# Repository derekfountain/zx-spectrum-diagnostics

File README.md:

# 16K/48K ZX Spectrum Diagnostics Board

This is a hardware diagnostics board for the 16K and 48K ZX Spectrum,
based on two Raspberry Pi Pico microcontroller boards.

The idea is that given a Spectrum of unknown provenance (an eBay
purchase maybe), this device can quickly tell you what potential
issues the Spectrum might have. It's limited to what it can see on the
rear edge connector, so it can't detect broken tracks or things like
that, but it can report a fair amount of useful information. There are
no guarantees, of course.

The board plugs into the Spectrum's rear edge connector, and has an OLED
screen and a single user-interface button:

The rear of the board carries the Picos and some header sockets (discussed below):

The board is powered by the Spectrum. You just plug it in and turn the
Spectrum on. It will (repeatedly) run a set of tests on the signals it
sees on the rear edge connector. The tests are divided into pages. Pressing
the button advances to the next page of tests.

Click through for a brief demonstration:

https://www.youtube.com/watch?v=3YdgdeM5kM0

## Status

As of March 2024, v1.2 is functionally complete. The KiCAD project here is current up
to v1.3 which just has a couple of silkscreen fixes.

There is plenty of scope to upgrade the tests the board runs, so updates
might appear in future. For now the board is complete.

[Derek Fountain](https://www.derekfountain.org/), March 2024

# Operation

The Spectrum is usable when the device is displaying the voltages page.
The tests which run on the other pages constantly reset the Spectrum
so it can't be used when any of those are showing.

The pages, and the tests run, are as follows. You might find it useful to
read the [Spectrum Service manual](https://spectrumforeveryone.com/wp-content/uploads/2017/08/ZX-Spectrum-Service-Manual.pdf)
in conjunction with the following.

## Voltages Page

Voltages are the first thing we look at when faced with a broken ZX Spectrum.
There are four voltages used: the input from the PSU, which is nominally +9V
and isn't analysed by the Picos; the main +5V supply for the Spectrum board;
the +12V supply for the RAM and video subsystem; and the -5V supply for the
RAM.

The OLED screen shows the voltages on the rear edge connector.
That's not the same as what's going on at the RAM chips! But it's a very good
indication, especially when you see faults being reported.

The top three lines of the display show the voltages as detected by the Pico's
analogue to digital converters. These values update several times a second. The
bottom three lines show the averages for those values over the last 100
samples. Note that the further the voltages get from the expected values, the
less accurate the reported values will be. This is because the circuitry on the
board is designed to protect the Picos from rogue voltages, as opposed to
providing accurate results in all circumstances.

The Picos are powered from the Spectrum's +5V so if that's not working
the Picos won't turn on and you probably won't have got this
far. Assuming the plug on the PSU is outputting 9V to 14V as you'd
expect, you probably have a faulty 7805 regulator.

The +12V and -5V supplies come from the Spectrum's internal DC/DC
converters. They're known to be a bit wobbly, and the -5V supply in particular
has a rather wide tolerance (-5.5V to -4.0V, see the service manual).

Here's a screen showing the voltages from a broken Spectrum. The -5V supply is
within specification, but the 12V supply is broken:

Note: if the Spectrum's internal voltage regulator has failed in such
a way that the Spectrum's internal +5V supply is too high, that high
voltage will be fed into the Picos and might destroy them. The maximum
they can take is +5.5V. I've never heard of a 7805 regulator failing
in this way, and if one does the Spectrum it's inside will be very
dead, but if you think it might have happened you should check the +5V
on the edge connector before connecting the Picos to it. (Remove the
Picos, plug the board in to the Spectrum, then check the +5V line at
any of the +5V sample points.)

## ULA Page

The ULA does a lot of stuff inside the Spectrum, and can fail in whole
or in part. i.e. some parts of its internal circuitry can be working while other
parts are dead. A partially working ULA can be rather puzzling to
diagnose. The tests on the diagnostics board only test the clocks the
ULA is emitting.

The INT clock is the Spectrum's interrupt clock. It's used to generate
both the TV picture and the Z80's interrupt signal. What's sampled
from the edge connector is directly from the ULA and should be exactly
50Hz.

The CLK is the Z80's clock, which is also generated by the ULA. This should be
3.5MHz. The diagnostics board samples the signal using the RP2040's PIOs, and
is (internally) accurate to a single clock cycle. This is sampled with the Z80
held in reset, so the Spectrum's notorious memory contention doesn't get in
the way (see next item).

The cCLK is the contended clock, which is the clock signal the ULA provides for
the Z80 when the ULA and memory chips clash trying to read lower memory. This will
always be slightly slower than the CLK signal. This is sampled when the Z80 is
allowed to run normally, which means the ROM code is running and is updating
the screen and system variables which are in lower RAM. Some contention should
always be reported. Holding the space key down while the test is running
changes the contention pattern:

## Z80 Page

A subset of the Z80 signals are exposed on the Spectrum's rear edge connector:
read, write, memory read, and I/O request. Their exact behaviour aren't analysed (but
could be).

The Spectrum is allowed to start normally, then the Z80 signals are checked to ensure
they are transiting from low to high state, and from high to low state. Any
stuck signal will be reported, and would explain a failure of the Spectrum. Look for
solder bridges from botched repairs, or broken tracks.

The M1 line is an exception. Sinclair used some Z80s with non-functioning M1 signals,
and machines with those faulty Z80s can't drive certain peripherals like the Interface
One and my [recreated ZX Spectrum Expansion System](https://www.derekfountain.org/zses.php). The Spectrum can otherwise function
correctly, so a fault reported with the M1 line isn't that unusual and doesn't indicate
a fault which would stop the machine working.

## Data Bus Page

This test allows the Spectrum to start normally, then the Z80 data bus signals are
checked to ensure they are transiting from low to high state, and from high to low
state. Any stuck signal will be reported, and would explain a failure of the Spectrum.
The most likely cause would be a faulty memory chip holding its output bit high or
low, but also look for solder bridges from botched repairs, or broken tracks.

If the Spectrum has a faulty ROM or some other unusual fault it would still be likely
that whatever was appearing on the data bus would consist of state changes of all the
lines, at least occasionally. Therefore this test should be able to indicate stuck
lines reasonably reliably even in the presence of other faults.

## Address Bus Page

This test allows the Spectrum to start normally, then the Z80 address bus signals are
checked to ensure they are transiting from low to high state, and from high to low
state. Any stuck signal will be reported, and would explain a failure of the Spectrum.

The early code in the Spectrum's ROM does a RAM check which writes and reads from the
whole 64K address space, so all the address lines should transit within a second or so
of the machine starting up.

The ULA's signals on the address bus aren't exposed on the edge connector. What is
reported here is the Z80's perspective.

## ROM Page

This page runs a single test which checks whether the ROM appears to be providing
the correct data to the Z80 (i.e. the program which implements the Spectrum's BASIC
interpreter).

It allows the Spectrum to start, then samples the address bus watching for reads of
bytes from the ROM. Those addresses are collected, then analysed to see if they follow
the expected pattern. The Z80 code at the start of the Spectrum's ROM disables
interrupts, primes a couple of registers, then jumps to an absolute (hardcoded)
location. It's therefore possible to check whether the Z80 is requesting the bytes at
0x0000 to 0x0007 one at a time in sequence, then requests the byte at 0x11CB (which is
where the jump goes to) and so on.

It only samples a couple of dozen addresses to check the Z80 is following the expected
sequence, but if it is that means the Z80, and its control, data and address buses
are all functioning correctly or very close to correctly.

# ZX Signal Headers

The board has 3 rows of 20 pins which make accessible the Z80 and
Spectrum control signals which are on the rear edge connector, plus a
few more from the board itself.  They're labelled J201, J202 and
J203. All except one (~12V) of the Spectrum's edge connector signals
are brought out to these connectors (and that missing ~12V line could
now be fixed because after a juggle around I found a couple of spare
connections - see the errata.txt file).

These headers allow jumper wires to be inserted which enable easy
connection to a meter or oscilloscope. I've found this very
handy. This photo shows oscilloscope probing of the Z80 clock and
another signal from a board I got from eBay. Note the silver tab on
the corner of the board is a ground point for attaching clips to.

# Bill of Materials

This is a simple build. You will need:

3x [3216 SMD Diode](https://www.mouser.co.uk/ProductDetail/581-SD1206S040S2R0)
Schottky Diode for Pico input protection and 12V clamping
<br>
1x [PMBT2222A SMD Transistor](https://www.mouser.co.uk/ProductDetail/771-PMBT2222A-T-R)
NPN Transistor for /RESET
<br>
1x [3216 SMD 1K Resistor](https://www.mouser.co.uk/ProductDetail/603-RT1206FRE071KL)
1K Resistor for /RESET
<br>
3x [3216 SMD 1K5 Resistor](https://www.mouser.co.uk/ProductDetail/603-RT1206FRE071K5L)
1K5 Resistor for the voltage dividers
<br>
1x [3216 SMD 390R Resistor](https://www.mouser.co.uk/ProductDetail/603-RT1206FRE07390RL)
390R Resistor for the voltage divider
<br>
1x [3216 SMD 5K6 Resistor](https://www.mouser.co.uk/ProductDetail/603-RT1206FRE075K6L)
5K6 Resistor for the voltage divider
<br>

Also, from your parts bin:

2x Raspberry Pi Pico with pins and sockets if you want them
<br>
1x 4-pin header and socket for mounting the screen
<br>
1x SPST switch. Any single pole, single throw switch should do for the user input
<br>
1x 0.96" OLED display (SSH1106 based if you want to use my code)

Note that the OLED screen I used is SSH1106 based. It's actually got SSD1306
printed on it, which was an unpleasant surprise at the time. If you want to
use one of the more common SSD1306 based screens the software will need
updating. It's only displaying text so that shouldn't be too difficult.

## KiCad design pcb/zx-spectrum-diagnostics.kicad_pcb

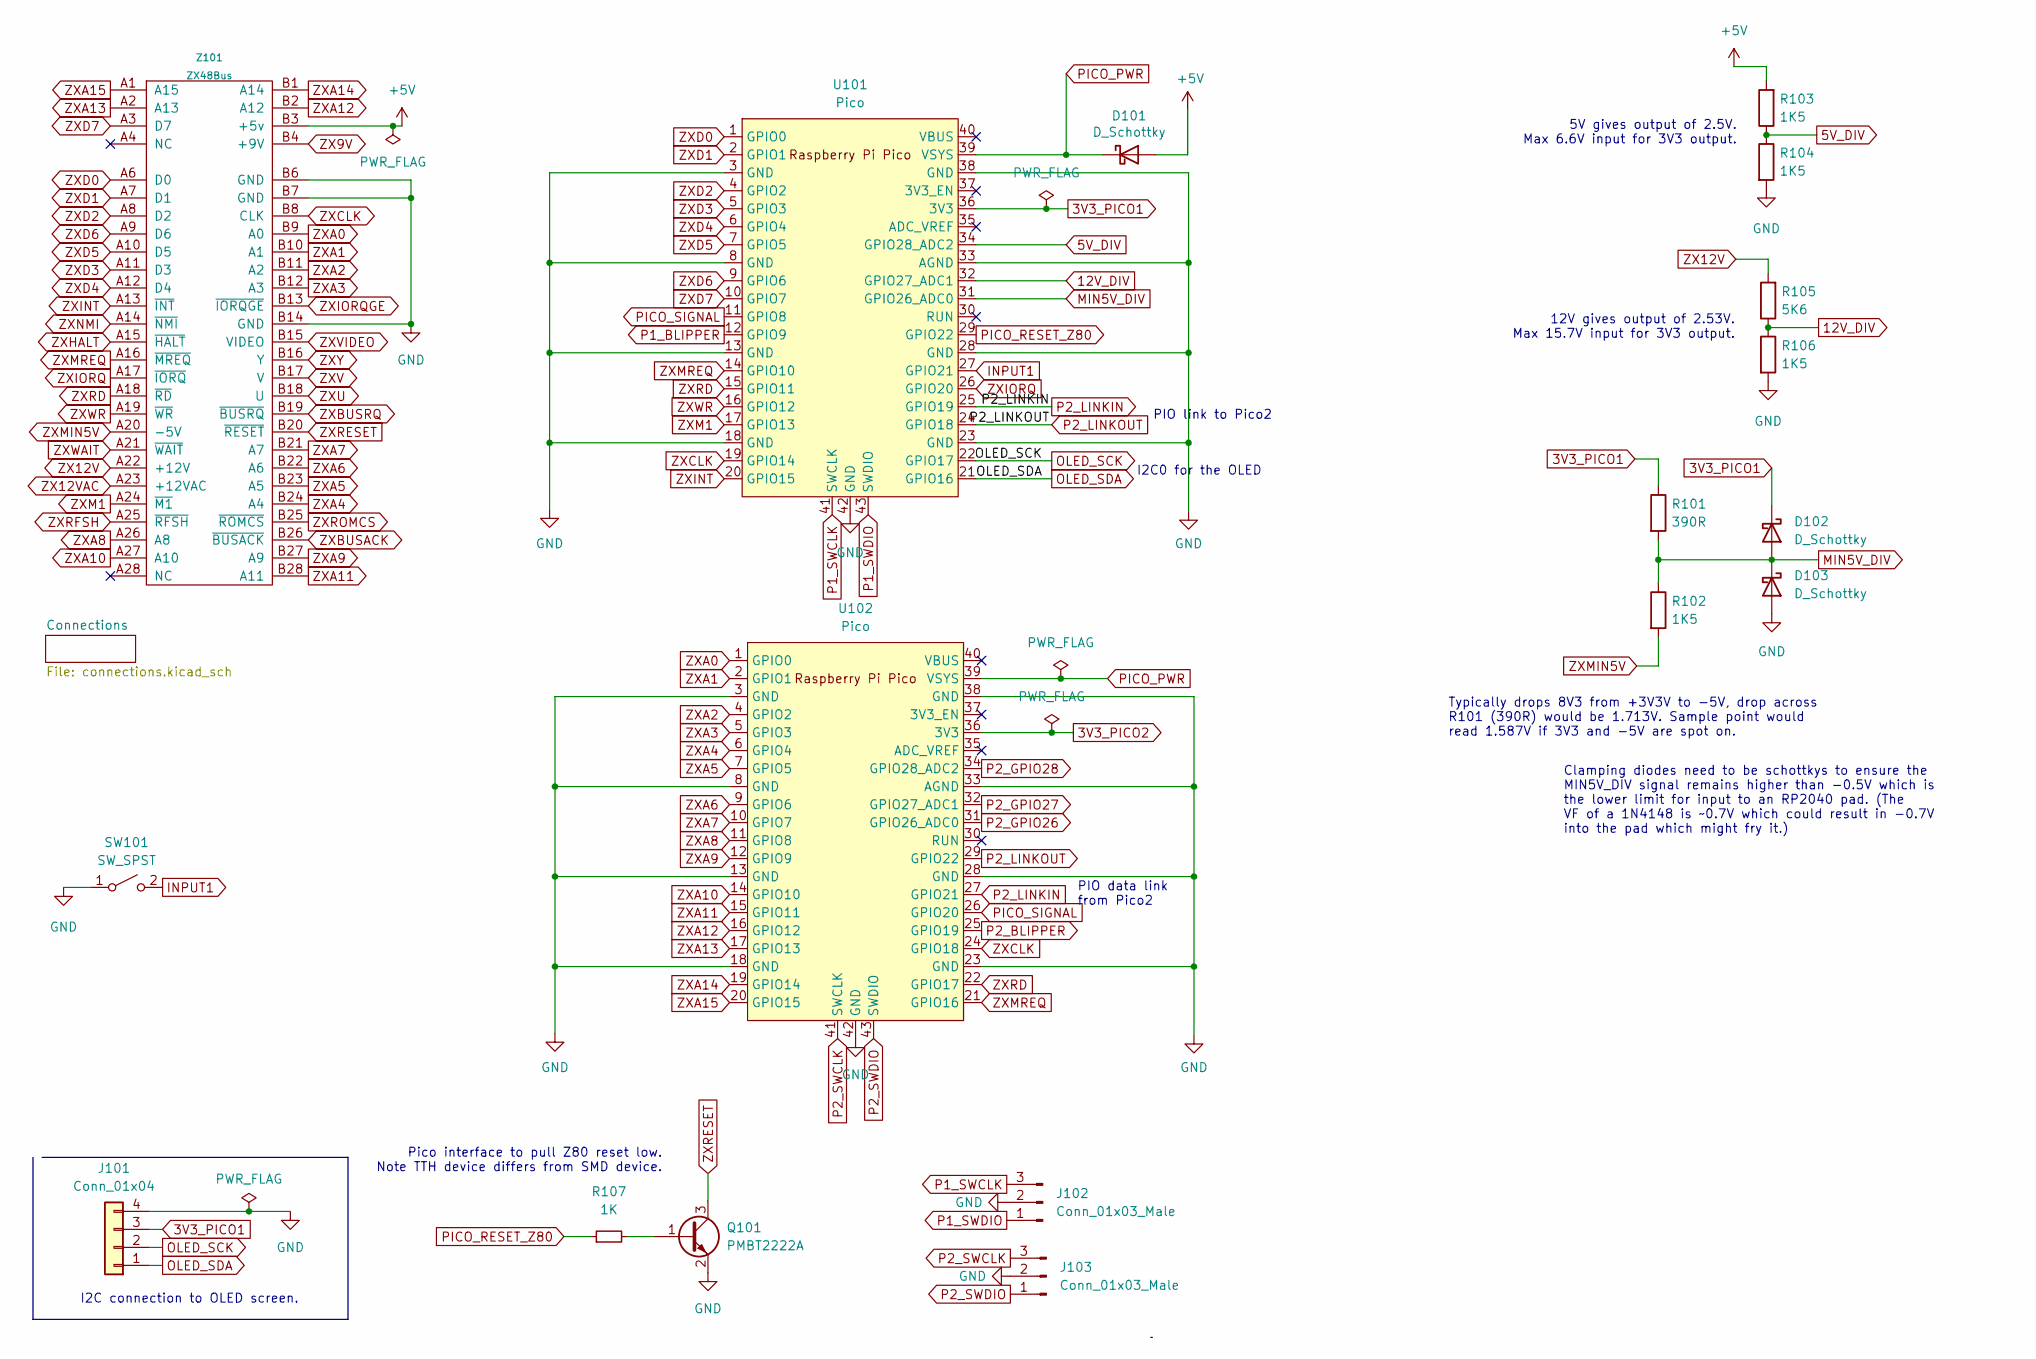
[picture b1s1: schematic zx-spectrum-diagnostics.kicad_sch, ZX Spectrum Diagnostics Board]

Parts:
D101, D102, D103: D_Schottky; D_1206_3216Metric_Pad1.42x1.75mm_HandSolder
J101: Conn_01x04; PinHeader_1x04_P2.54mm_Vertical
J102, J103: Conn_01x03_Male; PinSocket_1x03_P2.54mm_Vertical
Q101: PMBT2222A; TSOT-23_HandSoldering
R101: 390R; R_1206_3216Metric_Pad1.30x1.75mm_HandSolder
R102, R103, R104, R106: 1K5; R_1206_3216Metric_Pad1.30x1.75mm_HandSolder
R105: 5K6; R_1206_3216Metric_Pad1.30x1.75mm_HandSolder
R107: 1K; R_1206_3216Metric_Pad1.30x1.75mm_HandSolder
SW101: SW_SPST; SW_PUSH_6mm_H4.3mm
U101, U102: Pico; RPi_Pico_SMD_TH
Z101: ZX48Bus; Spectrum_Edge_Connector

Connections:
3V3_PICO1: D102.1 (K), J101.3, R101.1, U101.36 (3V3)
3V3_PICO2: U102.36 (3V3)
5V_DIV: R103.1, R104.1, U101.34 (GPIO28_ADC2); also elsewhere on the board
12V_DIV: R105.1, R106.1, U101.32 (GPIO27_ADC1); also elsewhere on the board
+5V: D101.2 (A), R103.2, Z101.B3 (+5v); also elsewhere on the board
GND: D103.2 (A), J101.4, J102.2, J103.2, Q101.2 (E), R104.2, R106.2, SW101.1 (A), U101.3 (GND), U101.8 (GND), U101.13 (GND), U101.18 (GND), U101.23 (GND), U101.28 (GND), U101.33 (AGND), U101.38 (GND), U101.42 (GND), U102.3 (GND), U102.8 (GND), U102.13 (GND), U102.18 (GND), U102.23 (GND), U102.28 (GND), U102.33 (AGND), U102.38 (GND), U102.42 (GND), Z101.B6 (GND), Z101.B7 (GND), Z101.B14 (GND)
INPUT1: SW101.2 (B), U101.27 (GPIO21)
MIN5V_DIV: D102.2 (A), D103.1 (K), R101.2, R102.1, U101.31 (GPIO26_ADC0); also elsewhere on the board
unnamed: Q101.1 (B), R107.2
OLED_SCK: J101.2, U101.22 (GPIO17)
OLED_SDA: J101.1, U101.21 (GPIO16)
P1_BLIPPER: U101.12 (GPIO9); also elsewhere on the board
P1_SWCLK: J102.3, U101.41 (SWCLK)
P1_SWDIO: J102.1, U101.43 (SWDIO)
P2_BLIPPER: U102.25 (GPIO19); also elsewhere on the board
P2_GPIO26: U102.31 (GPIO26_ADC0); also elsewhere on the board
P2_GPIO27: U102.32 (GPIO27_ADC1); also elsewhere on the board
P2_GPIO28: U102.34 (GPIO28_ADC2); also elsewhere on the board
P2_LINKIN: U101.25 (GPIO19), U102.27 (GPIO21)
P2_LINKOUT: U101.24 (GPIO18), U102.29 (GPIO22)
P2_SWCLK: J103.3, U102.41 (SWCLK)
P2_SWDIO: J103.1, U102.43 (SWDIO)
PICO_PWR: D101.1 (K), U101.39 (VSYS), U102.39 (VSYS)
PICO_RESET_Z80: R107.1, U101.29 (GPIO22)
PICO_SIGNAL: U101.11 (GPIO8), U102.26 (GPIO20); also elsewhere on the board
ZX9V: Z101.B4 (+9V); also elsewhere on the board
ZX12V: R105.2, Z101.A22 (+12V); also elsewhere on the board
ZX12VAC: Z101.A23 (+12VAC)
ZXA0: U102.1 (GPIO0), Z101.B9 (A0); also elsewhere on the board
ZXA1: U102.2 (GPIO1), Z101.B10 (A1); also elsewhere on the board
ZXA2: U102.4 (GPIO2), Z101.B11 (A2); also elsewhere on the board
ZXA3: U102.5 (GPIO3), Z101.B12 (A3); also elsewhere on the board
ZXA4: U102.6 (GPIO4), Z101.B24 (A4); also elsewhere on the board
ZXA5: U102.7 (GPIO5), Z101.B23 (A5); also elsewhere on the board
ZXA6: U102.9 (GPIO6), Z101.B22 (A6); also elsewhere on the board
ZXA7: U102.10 (GPIO7), Z101.B21 (A7); also elsewhere on the board
ZXA8: U102.11 (GPIO8), Z101.A26 (A8); also elsewhere on the board
ZXA9: U102.12 (GPIO9), Z101.B27 (A9); also elsewhere on the board
ZXA10: U102.14 (GPIO10), Z101.A27 (A10); also elsewhere on the board
ZXA11: U102.15 (GPIO11), Z101.B28 (A11); also elsewhere on the board
ZXA12: U102.16 (GPIO12), Z101.B2 (A12); also elsewhere on the board
ZXA13: U102.17 (GPIO13), Z101.A2 (A13); also elsewhere on the board
ZXA14: U102.19 (GPIO14), Z101.B1 (A14); also elsewhere on the board
ZXA15: U102.20 (GPIO15), Z101.A1 (A15); also elsewhere on the board
ZXBUSACK: Z101.B26 (~BUSACK); also elsewhere on the board
ZXBUSRQ: Z101.B19 (~BUSRQ); also elsewhere on the board
ZXCLK: U101.19 (GPIO14), U102.24 (GPIO18), Z101.B8 (CLK); also elsewhere on the board
ZXD0: U101.1 (GPIO0), Z101.A6 (D0); also elsewhere on the board
ZXD1: U101.2 (GPIO1), Z101.A7 (D1); also elsewhere on the board
ZXD2: U101.4 (GPIO2), Z101.A8 (D2); also elsewhere on the board
ZXD3: U101.5 (GPIO3), Z101.A11 (D3); also elsewhere on the board
ZXD4: U101.6 (GPIO4), Z101.A12 (D4); also elsewhere on the board
ZXD5: U101.7 (GPIO5), Z101.A10 (D5); also elsewhere on the board
ZXD6: U101.9 (GPIO6), Z101.A9 (D6); also elsewhere on the board
ZXD7: U101.10 (GPIO7), Z101.A3 (D7); also elsewhere on the board
ZXHALT: Z101.A15 (~HALT); also elsewhere on the board
ZXINT: U101.20 (GPIO15), Z101.A13 (~INT); also elsewhere on the board
ZXIORQ: U101.26 (GPIO20), Z101.A17 (~IORQ); also elsewhere on the board
ZXIORQGE: Z101.B13 (~IORQGE); also elsewhere on the board
ZXM1: U101.17 (GPIO13), Z101.A24 (~M1); also elsewhere on the board
ZXMIN5V: R102.2, Z101.A20 (-5V); also elsewhere on the board
ZXMREQ: U101.14 (GPIO10), U102.21 (GPIO16), Z101.A16 (~MREQ); also elsewhere on the board
ZXNMI: Z101.A14 (~NMI); also elsewhere on the board
ZXRD: U101.15 (GPIO11), U102.22 (GPIO17), Z101.A18 (~RD); also elsewhere on the board
ZXRESET: Q101.3 (C), Z101.B20 (~RESET); also elsewhere on the board
ZXRFSH: Z101.A25 (~RFSH); also elsewhere on the board
ZXROMCS: Z101.B25 (~ROMCS); also elsewhere on the board
ZXU: Z101.B18 (U); also elsewhere on the board
ZXV: Z101.B17 (V); also elsewhere on the board
ZXVIDEO: Z101.B15 (VIDEO); also elsewhere on the board
ZXWAIT: Z101.A21 (~WAIT); also elsewhere on the board
ZXWR: U101.16 (GPIO12), Z101.A19 (~WR); also elsewhere on the board
ZXY: Z101.B16 (Y); also elsewhere on the board

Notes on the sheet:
5V gives output of 2.5V. Max 6.6V input for 3V3 output.
PIO data link from Pico2
I2C connection to OLED screen.
I2C0 for the OLED
PIO link to Pico2
Pico interface to pull Z80 reset low. Note TTH device differs from SMD device.
Typically drops 8V3 from +3V3V to -5V, drop across R101 (390R) would be 1.713V. Sample point would read 1.587V if 3V3 and -5V are spot on.
Clamping diodes need to be schottkys to ensure the MIN5V_DIV signal remains higher than -0.5V which is the lower limit for input to an RP2040 pad. (The VF of a 1N4148 is ~0.7V which could result in -0.7V into the pad which might fry it.)
12V gives output of 2.53V. Max 15.7V input for 3V3 output.

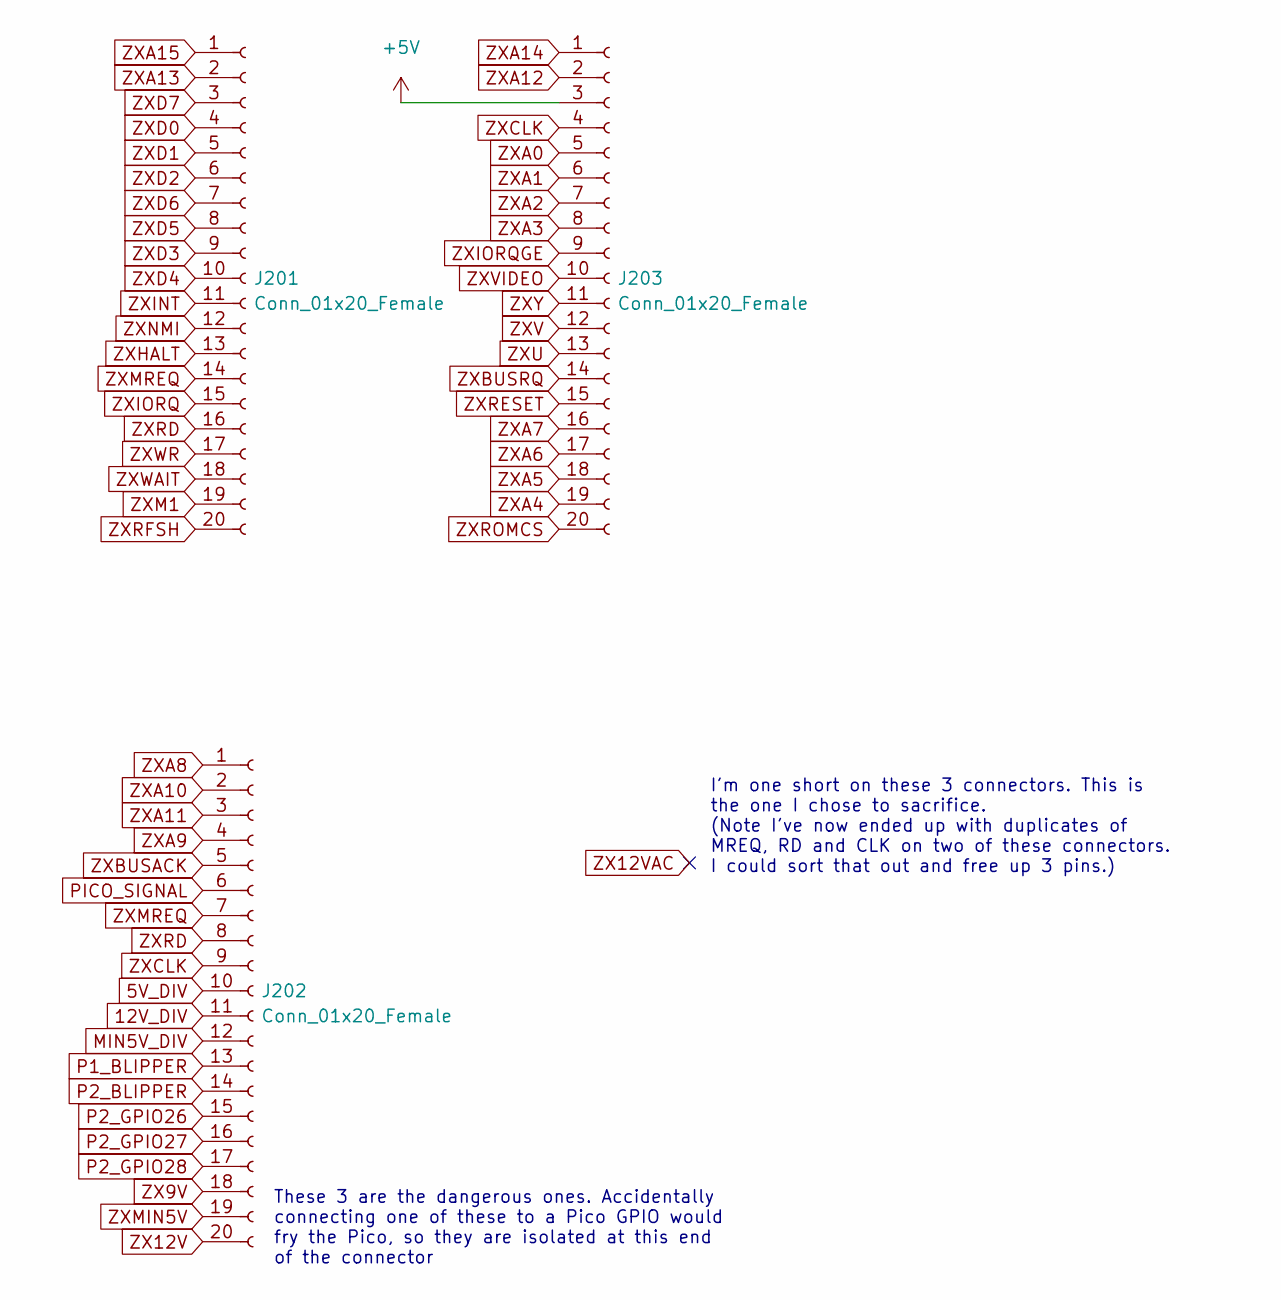
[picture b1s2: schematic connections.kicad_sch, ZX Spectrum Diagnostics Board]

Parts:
J201, J202, J203: Conn_01x20_Female; PinSocket_1x20_P2.54mm_Vertical

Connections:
5V_DIV: J202.10; also elsewhere on the board
12V_DIV: J202.11; also elsewhere on the board
+5V: J203.3; also elsewhere on the board
MIN5V_DIV: J202.12; also elsewhere on the board
P1_BLIPPER: J202.13; also elsewhere on the board
P2_BLIPPER: J202.14; also elsewhere on the board
P2_GPIO26: J202.15; also elsewhere on the board
P2_GPIO27: J202.16; also elsewhere on the board
P2_GPIO28: J202.17; also elsewhere on the board
PICO_SIGNAL: J202.6; also elsewhere on the board
ZX9V: J202.18; also elsewhere on the board
ZX12V: J202.20; also elsewhere on the board
ZXA0: J203.5; also elsewhere on the board
ZXA1: J203.6; also elsewhere on the board
ZXA2: J203.7; also elsewhere on the board
ZXA3: J203.8; also elsewhere on the board
ZXA4: J203.19; also elsewhere on the board
ZXA5: J203.18; also elsewhere on the board
ZXA6: J203.17; also elsewhere on the board
ZXA7: J203.16; also elsewhere on the board
ZXA8: J202.1; also elsewhere on the board
ZXA9: J202.4; also elsewhere on the board
ZXA10: J202.2; also elsewhere on the board
ZXA11: J202.3; also elsewhere on the board
ZXA12: J203.2; also elsewhere on the board
ZXA13: J201.2; also elsewhere on the board
ZXA14: J203.1; also elsewhere on the board
ZXA15: J201.1; also elsewhere on the board
ZXBUSACK: J202.5; also elsewhere on the board
ZXBUSRQ: J203.14; also elsewhere on the board
ZXCLK: J202.9, J203.4; also elsewhere on the board
ZXD0: J201.4; also elsewhere on the board
ZXD1: J201.5; also elsewhere on the board
ZXD2: J201.6; also elsewhere on the board
ZXD3: J201.9; also elsewhere on the board
ZXD4: J201.10; also elsewhere on the board
ZXD5: J201.8; also elsewhere on the board
ZXD6: J201.7; also elsewhere on the board
ZXD7: J201.3; also elsewhere on the board
ZXHALT: J201.13; also elsewhere on the board
ZXINT: J201.11; also elsewhere on the board
ZXIORQ: J201.15; also elsewhere on the board
ZXIORQGE: J203.9; also elsewhere on the board
ZXM1: J201.19; also elsewhere on the board
ZXMIN5V: J202.19; also elsewhere on the board
ZXMREQ: J201.14, J202.7; also elsewhere on the board
ZXNMI: J201.12; also elsewhere on the board
ZXRD: J201.16, J202.8; also elsewhere on the board
ZXRESET: J203.15; also elsewhere on the board
ZXRFSH: J201.20; also elsewhere on the board
ZXROMCS: J203.20; also elsewhere on the board
ZXU: J203.13; also elsewhere on the board
ZXV: J203.12; also elsewhere on the board
ZXVIDEO: J203.10; also elsewhere on the board
ZXWAIT: J201.18; also elsewhere on the board
ZXWR: J201.17; also elsewhere on the board
ZXY: J203.11; also elsewhere on the board

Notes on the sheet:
These 3 are the dangerous ones. Accidentally connecting one of these to a Pico GPIO would fry the Pico, so they are isolated at this end of the connector
I'm one short on these 3 connectors. This is the one I chose to sacrifice. (Note I've now ended up with duplicates of MREQ, RD and CLK on two of these connectors. I could sort that out and free up 3 pins.)

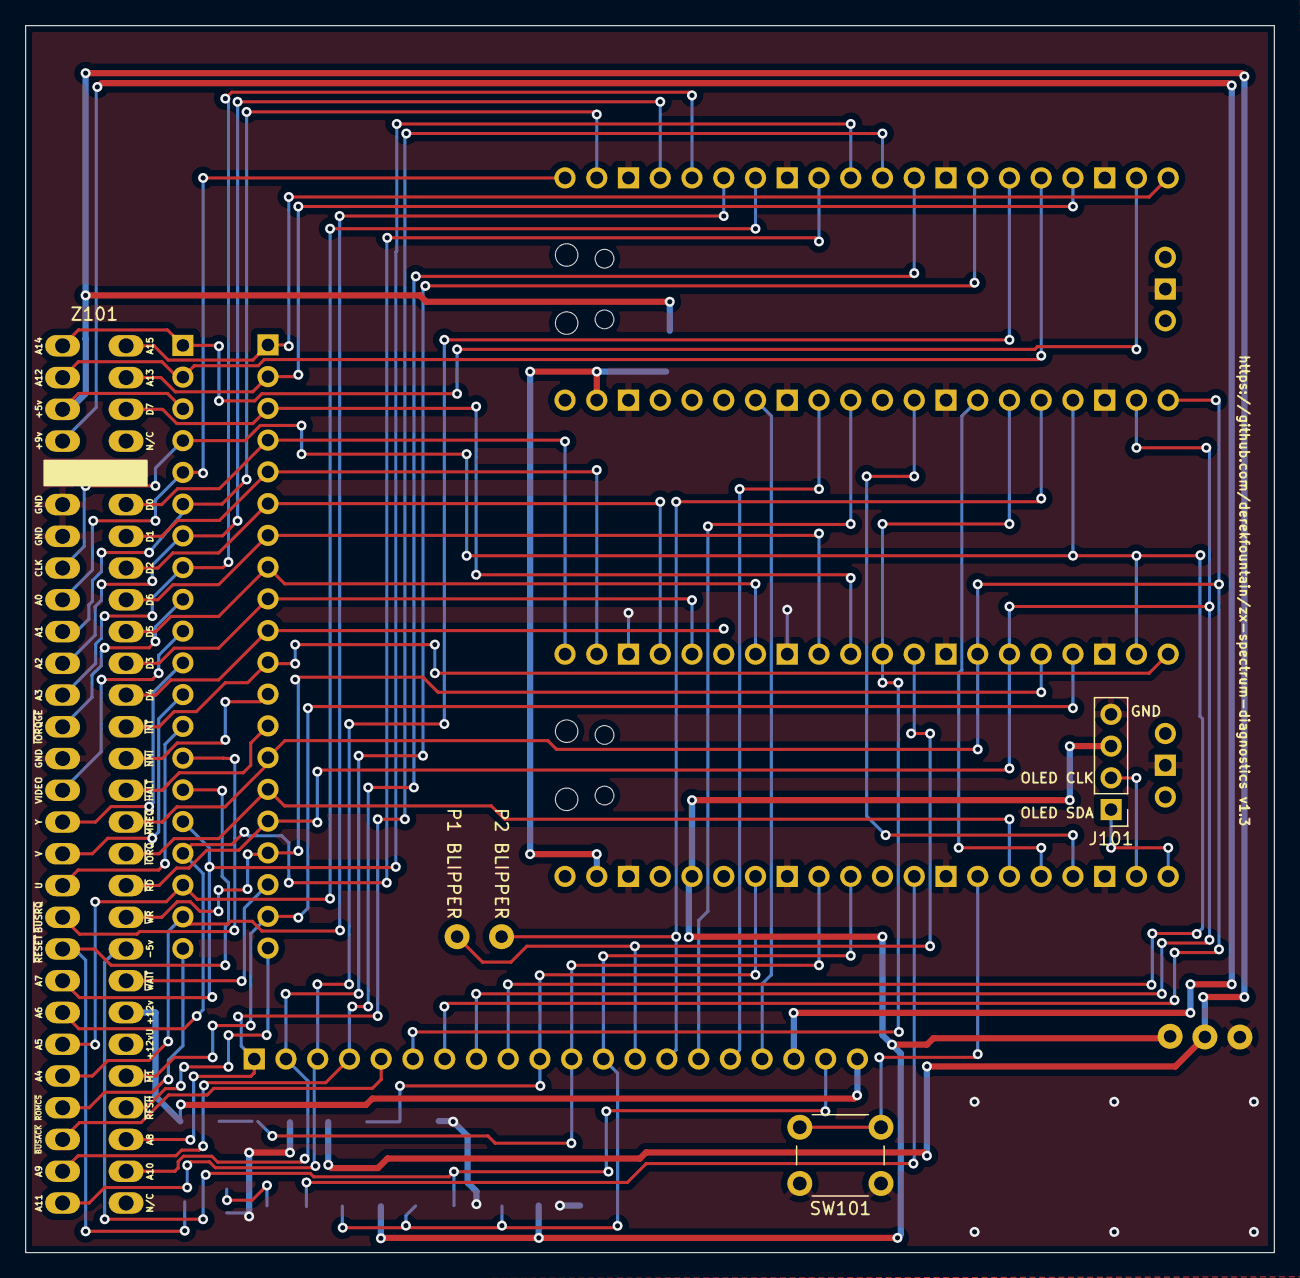
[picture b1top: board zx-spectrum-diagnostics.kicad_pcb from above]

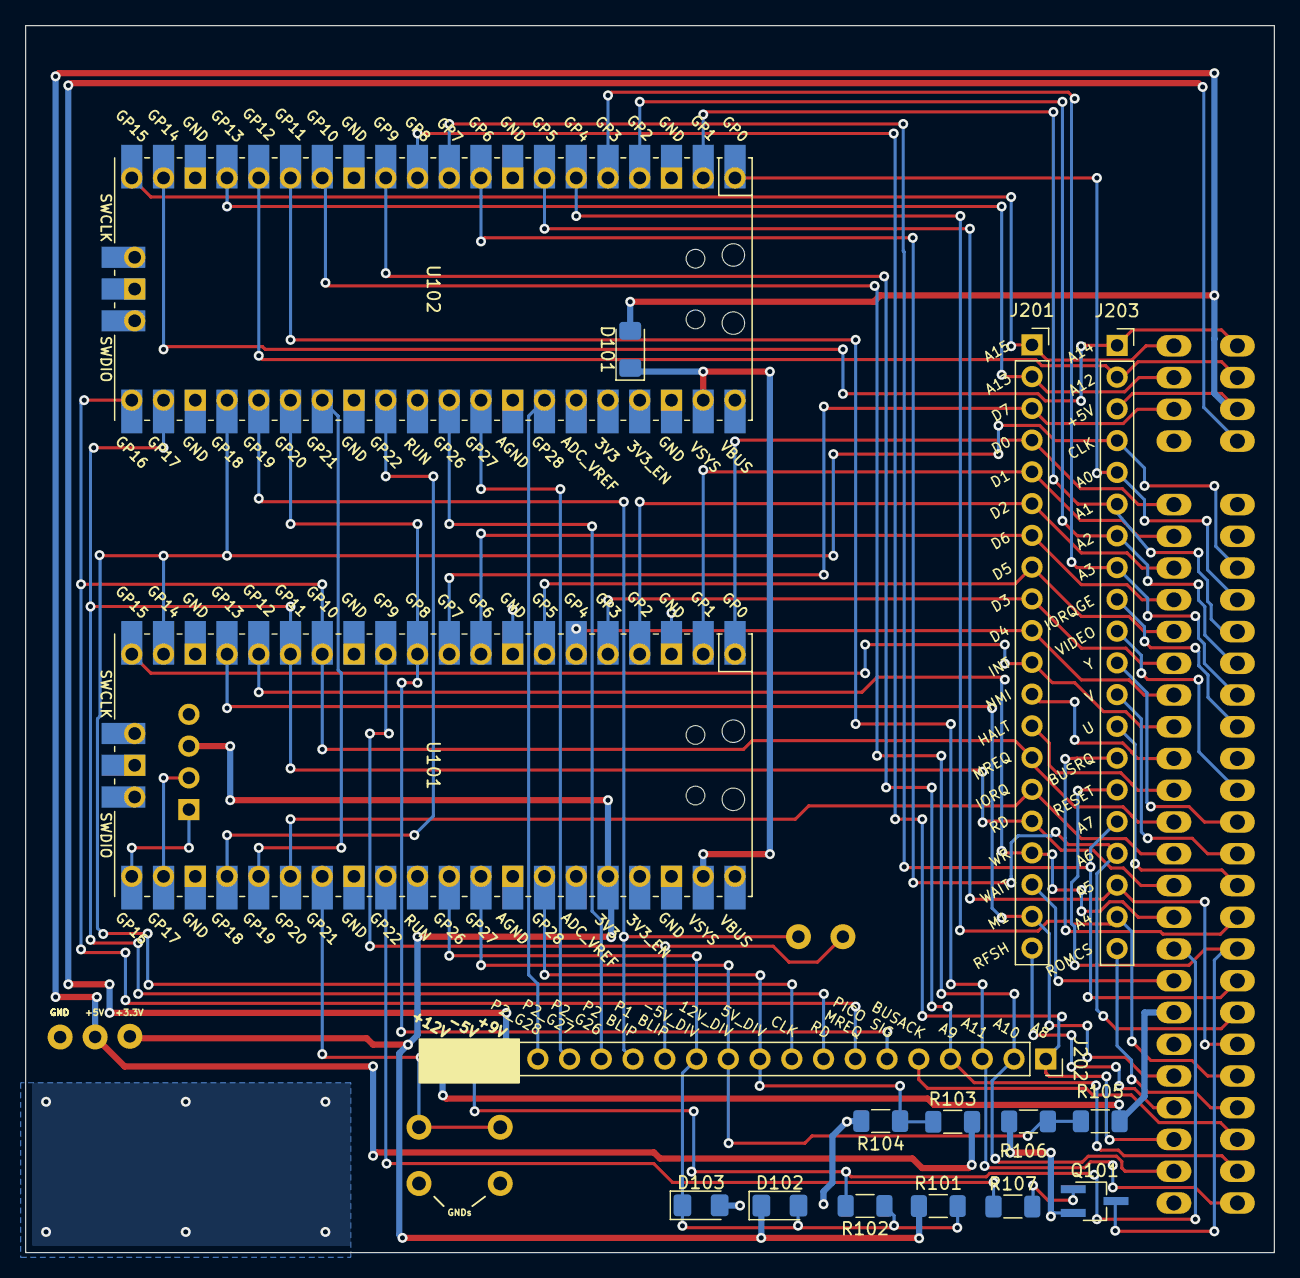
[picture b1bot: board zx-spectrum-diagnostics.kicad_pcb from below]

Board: 2 copper layers, 99.9 x 98.2 mm, 19 parts (16 on the bottom side), 67 nets.

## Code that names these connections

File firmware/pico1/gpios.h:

/* GPIOs for Pico1, the one with the data bus and most of the Z80 signals */

#ifndef __GPIOS_H
#define GPIOS_H

/* These need to match the hardware design */

/* Test signal to scope */
#define GPIO_P1_BLIPPER   9

/* I2C to screen */
#define GPIO_OLED_SDA    16
#define GPIO_OLED_SCK    17

/* Pico1 to Pico2 signal */
#define GPIO_P1_SIGNAL    8

/* Click on user button */
#define GPIO_INPUT1      21

/* Pico2 to Pico1 serial data link pin, input to Pico1 */
#define GPIO_P2_LINKOUT  18

/* Pico1 to Pico2 serial data link pin, input to Pico2 */
#define GPIO_P2_LINKIN   19

/* Output, holds Z80 in reset */
#define GPIO_Z80_RESET   22

#define GPIO_Z80_MREQ    10
#define GPIO_Z80_IORQ    20
#define GPIO_Z80_RD      11
#define GPIO_Z80_WR      12
#define GPIO_Z80_M1      13
#define GPIO_Z80_CLK     14
#define GPIO_Z80_INT     15

#define GPIO_DBUS_D0      0
#define GPIO_DBUS_D1      1
#define GPIO_DBUS_D2      2
#define GPIO_DBUS_D3      3
#define GPIO_DBUS_D4      4
#define GPIO_DBUS_D5      5
#define GPIO_DBUS_D6      6
#define GPIO_DBUS_D7      7

#endif

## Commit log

2023-10-29 import various bits from other projects
2023-10-29 update schematic, add a second pico, tidy -5V sampler
2023-10-29 first layout
2023-11-04 back out previous layout, rearrange connections to match edge connector
2023-11-04 relaid, complete, needs tidying
2023-11-04 lots more tidyups, nearly done
2023-11-05 final, ready for fab
2023-11-05 v1.0 off to fab
2023-11-12 import my OLED SH1106 demo as a starting point
2023-11-12 stab at using the 8x5 font, it's not as easy as I hoped
2023-11-12 8x5 font now working
2023-11-13 make some attempt to tidy up the oled mess, lots still to do
2023-11-13 build a bit of framework
2023-11-13 get a page reading voltages from the ADCs into place
2023-11-13 prepare some of the input button stuff
2023-11-14 add the scaling to the voltages, still no HW to test it on
2023-11-21 first board connected to spectrum, display working
2023-11-22 voltages displaying correctly on test machines
2023-11-22 change the layout to use the proper edge connector
2023-11-23 add the INT counter test on a ULA page
2023-11-26 simply the structure for calling the tests
2023-11-27 get the CLK counter PIO in place
2023-11-27 add blipper, get the CLK reporting correctly (reset must be held, wire came out)
2023-11-27 bit of tiding up
2023-11-28 use second PIO for cCLK, seems to work like that
2023-11-28 give up trying to use 1 state machine for both contended and non-contended CLK tests. it's working with separate SMs
2023-11-29 schematic reworked, it's time to relayout the board. checkpoint here
2023-11-29 sorted out the pico orientation and the edge connector connections
2023-11-30 just realised i've left J205 on the PCB! need to remove it and tidy up
2023-11-30 connections all in place, many tidyups required
2023-11-30 v1.1 ready to go? last checks
2023-11-30 v1.1 off for fabrication
2023-12-22 v1.1 of the board working as well as v1.0 ever did
2024-01-24 start to fix the PIO loading/unloading
2024-01-24 various tidyups of the ULA tests, looks good now
2024-01-25 soldered the switch to my board, very basic paging working
2024-01-25 tweak the debounce on the switch to try to stop it interfering with the INT counter, CLK and cCLK swapping is back
2024-01-25 nail the weird CLK/cCLK value swapping bug
2024-01-25 start the Z80 tests pages, M1 working
2024-01-26 more cleanups of the code, M1 test working, GPIO handling improved
2024-01-26 RD and WR working, but performance has been crippled
2024-01-29 split each page into an isolated test run, move user input handling to core1
2024-01-29 enable the MREQ test
2024-01-29 add page titles
2024-01-29 make control bus tests spot both rising and falling edges
2024-01-31 get dbus test working, not sure how to present the result
2024-01-31 add tests running message, tidy GUI a bit
2024-02-01 add ROM tests framework
2024-02-15 move display code into the modules
2024-02-15 add averages to voltages page
2024-02-17 fix the stale data being shown issue
2024-02-17 more refactoring the screen output, better handling of screen page switching
2024-02-17 better dbus test result, try to reflect stuck lines
2024-02-19 add beginnings of a new pcb design based on the PGA2040
2024-02-19 remove button2, reuse GPIO for ZXIORQ
2024-02-19 add IORQ test, now I have the hardware mod in place
2024-02-19 set up single GPIO signal pico1->pico2
2024-02-20 basic comms between the picos established
2024-02-21 set up 2 way comms, use acknowledged byte transport
2024-02-21 small buffer going over, with acks
2024-02-21 pico2 is now acting on signal gpio, and sending a length/buffer combination
2024-02-22 have a required test value sent over to pico2 at the start. add test code to fill the address buffer. works but shows the odd restarting effect i saw when i was doing the ROM emulator
2024-02-23 address bus test data going from pico2 to pico1, test in place but not yet tested
2024-02-29 address bus lines test working, hard to test
2024-02-29 ROM page enabled, dummy test and comms working
2024-03-04 ROM sequence read appears working
2024-03-07 debug for the -5V issue
2024-03-07 big tidy up, rom test now sends result value
2024-03-07 more notes and errata
2024-03-09 add some notes about the -5V voltage divider
2024-03-11 rework the code to handle the rejigged -5V voltage divider
2024-03-12 update schematic and PCB with revised -5V voltage divider
2024-03-12 update v1.2 pcb, add comments to PGS version, create v1.2 gerbers
2024-03-12 start documentation
2024-03-13 remove test points from v1.2, replace with GND area for clip. updated gerbers, sent for fabrication
2024-03-28 minor updates to labels on silkscreen
2024-03-28 update final images and readme
2024-03-28 add the UF2 images
2024-04-02 embed YT video in readme
